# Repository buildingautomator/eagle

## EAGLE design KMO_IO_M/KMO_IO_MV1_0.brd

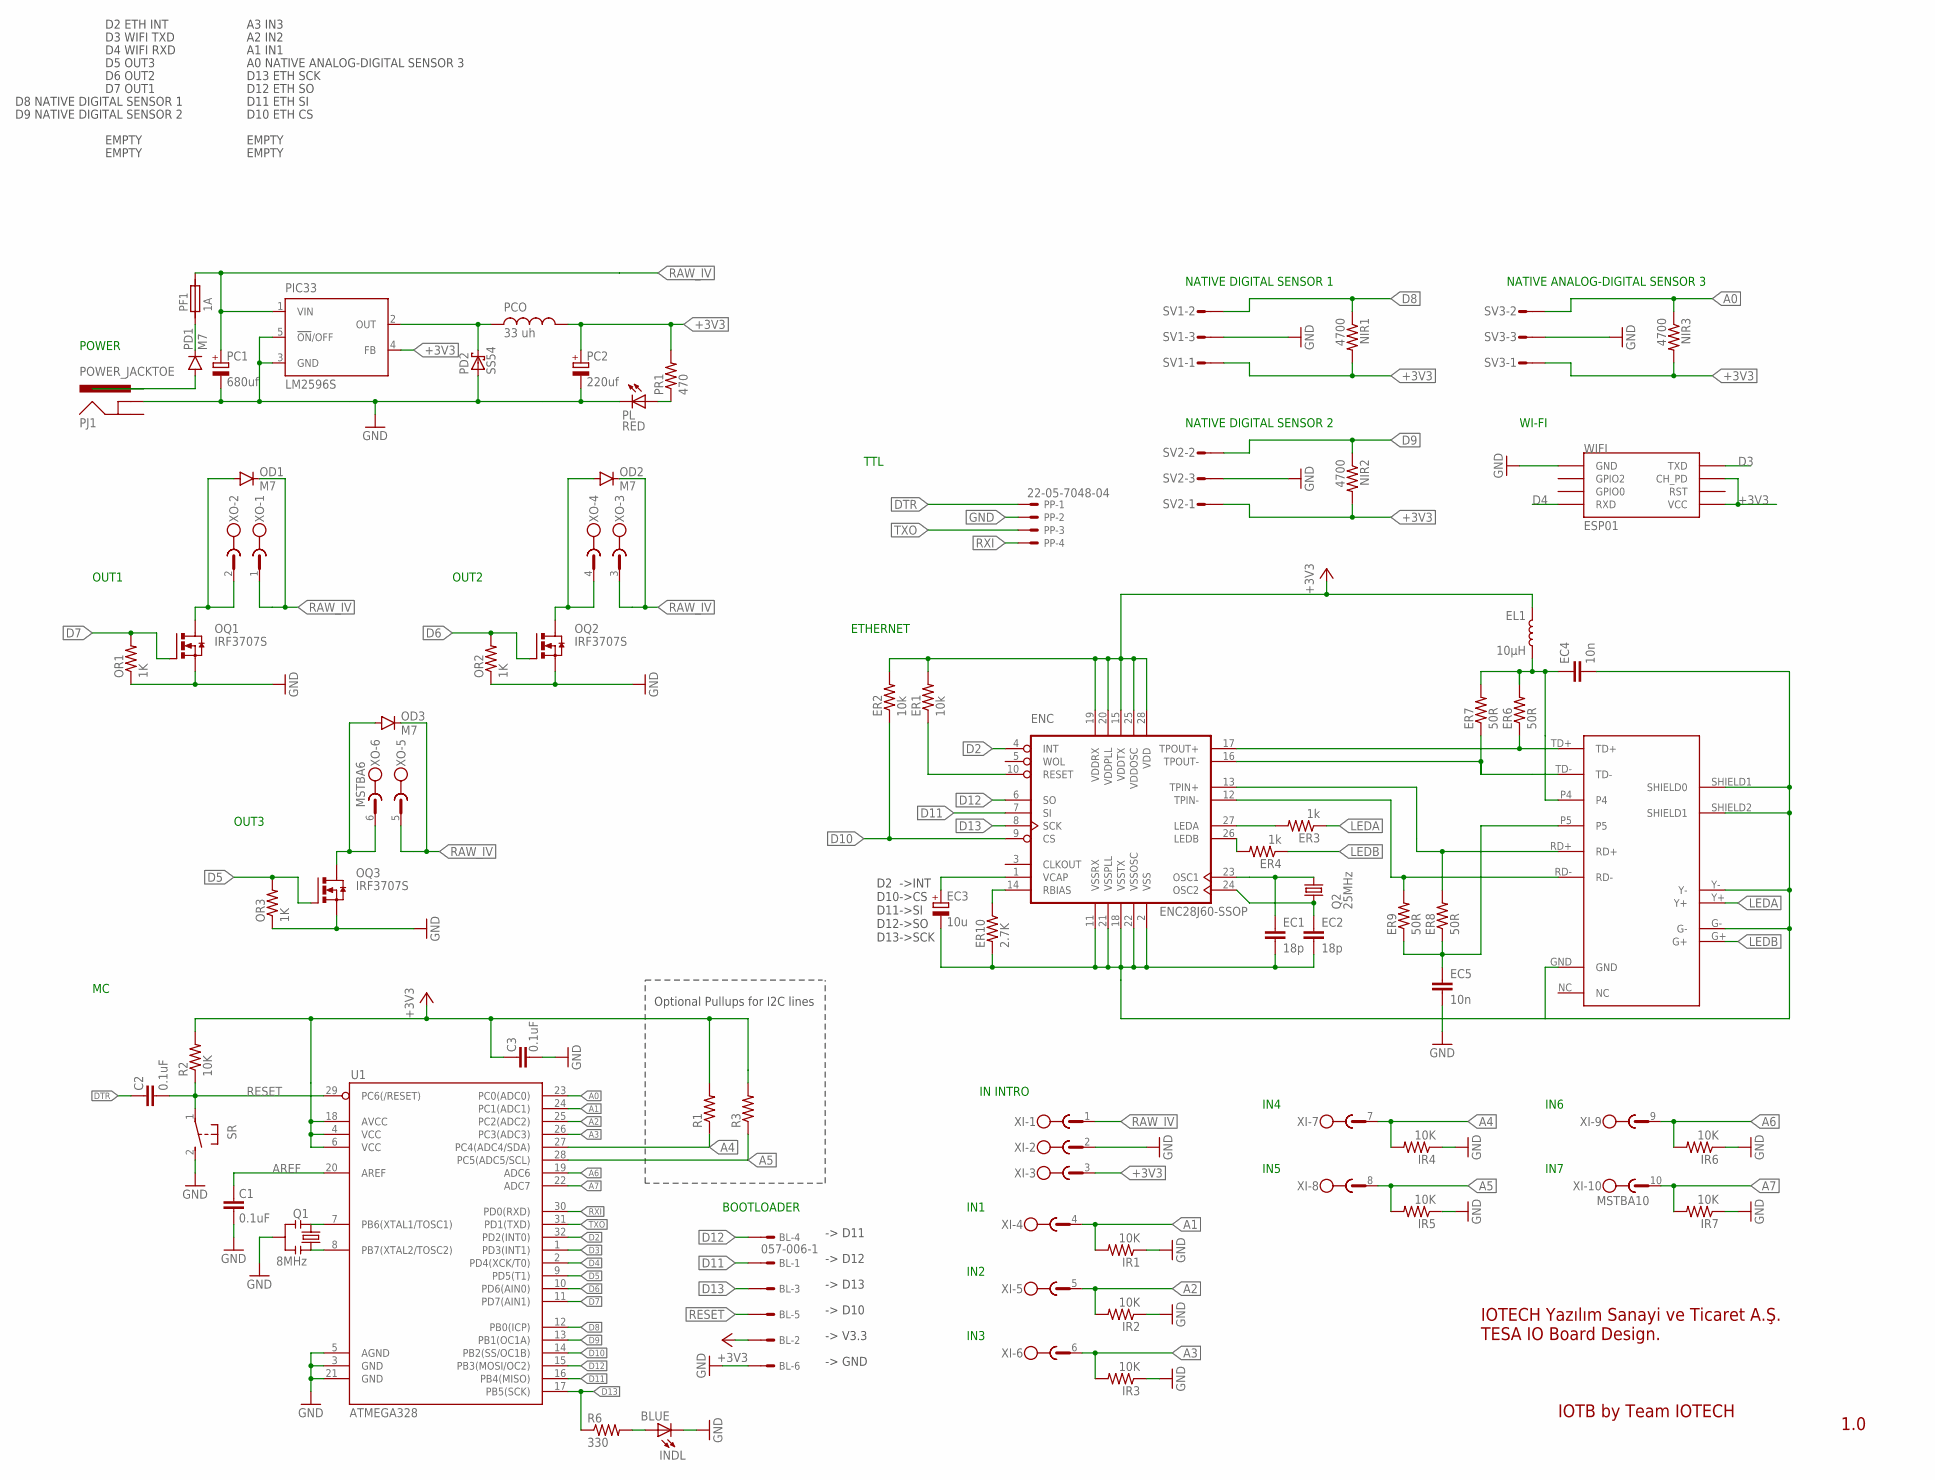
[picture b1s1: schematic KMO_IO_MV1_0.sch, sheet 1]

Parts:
BL: 057-006-1
C1, C2, C3: 0.1uF; 0805
EC1, EC2: 18p; 0805
EC3: 10u; CT3216
EC4, EC5: 10n; 0805
EL1: 10µH; 0805
ENC: ENC28J60-SSOP; SSOP28
ER1, ER2: 10k; 0805
ER3, ER4: 1k; 0805
ER6, ER7, ER8, ER9: 50R; 0805
ER10: 2.7K; 0805
INDL: BLUE; CHIP-LED0805
IR1, IR2, IR3, IR4, IR5, IR6, IR7: 10K; 0805
NIR1, NIR2, NIR3: 4700; 0805
OD1, OD2, OD3: M7; SMA-DIODE
OQ1, OQ2, OQ3: IRF3707S; D2PACK
OR1, OR2, OR3: 1K; 0805
PC1: 680uf; 140CLH-1010
PC2: 220uf; 140CLH-1010
PCO: 33 uh; MSS1260
PD1: M7; SMA-DIODE
PD2: SS54; SMB
PF1: 1A; 1820
PIC33: LM2596S; TO263-5
PJ1: POWER_JACKTOE; POWER_JACK_SMD_OVERPASTE_TOE
PL: RED; CHIP-LED0805
PP: 22-05-7048-04; 7395-04
PR1: 470; 0805
Q1: 8MHz; RESONATOR-SMD-1:1
Q2: 25MHz; 5.0X3.2_2
R1, R3: RESISTOR0805-RES; 0805
R2: 10K; 0805
R6: 330; 0805
SR: 31-XX; B3F-31XX
SV1, SV2, SV3: S03P
U1: ATMEGA328; TQFP32-08
U$2: HR911105A; RJ45
WIFI: ESP01
XI: MSTBA10
XO: MSTBA6

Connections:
+3V3: BL.2, C3.2, EL1.1, ENC.15 (VDDTX), ENC.19 (VDDRX), ENC.20 (VDDPLL), ENC.25 (VDDOSC), ENC.28 (VDD), ER1.2, ER2.2, NIR1.2, NIR2.2, NIR3.2, PC2.+, PCO.P$1, PIC33.4 (FB), PR1.2, R1.2, R2.2, R3.2, SV1.1, SV2.1, SV3.1, U1.4 (VCC), U1.6 (VCC), U1.18 (AVCC), WIFI.CH_PD, WIFI.VCC, XI.3
A0: NIR3.1, SV3.2, U1.23 (PC0(ADC0))
A1: IR1.2, U1.24 (PC1(ADC1)), XI.4
A2: IR2.2, U1.25 (PC2(ADC2)), XI.5
A3: IR3.2, U1.26 (PC3(ADC3)), XI.6
A4: IR4.2, R1.1, U1.27 (PC4(ADC4/SDA)), XI.7
A5: IR5.2, R3.1, U1.28 (PC5(ADC5/SCL)), XI.8
A6: IR6.2, U1.19 (ADC6), XI.9
A7: IR7.2, U1.22 (ADC7), XI.10
AREF: C1.2, U1.20 (AREF)
D2: ENC.4 (INT), U1.32 (PD2(INT0))
D3: U1.1 (PD3(INT1)), WIFI.TX (TXD)
D4: U1.2 (PD4(XCK/T0)), WIFI.RX (RXD)
D5: OQ3.1 (G), OR3.2, U1.9 (PD5(T1))
D6: OQ2.1 (G), OR2.2, U1.10 (PD6(AIN0))
D7: OQ1.1 (G), OR1.2, U1.11 (PD7(AIN1))
D8: NIR1.1, SV1.2, U1.12 (PB0(ICP))
D9: NIR2.1, SV2.2, U1.13 (PB1(OC1A))
D10: ENC.9 (CS), ER2.1, U1.14 (PB2(SS/OC1B))
D11: BL.1, ENC.7 (SI), U1.16 (PB4(MISO))
D12: BL.4, ENC.6 (SO), U1.15 (PB3(MOSI/OC2))
D13: BL.3, ENC.8 (SCK), R6.1, U1.17 (PB5(SCK))
DTR: C2.2, PP.1
EP4: EC4.1, EL1.2, ER6.2, ER7.2, U$2.P4
EP5: EC5.1, ER8.1, ER9.1, U$2.P5
GND: BL.6, C1.1, C3.1, EC1.2, EC2.2, EC3.-, EC4.2, EC5.2, ENC.2 (VSS), ENC.11 (VSSRX), ENC.18 (VSSTX), ENC.21 (VSSPLL), ENC.22 (VSSOSC), ER10.2, INDL.C, IR1.1, IR2.1, IR3.1, IR4.1, IR5.1, IR6.1, IR7.1, OQ1.3 (S), OQ2.3 (S), OQ3.3 (S), OR1.1, OR2.1, OR3.1, PC1.-, PC2.-, PD2.A, PIC33.3 (GND), PIC33.5 (!ON!/OFF), PJ1.GND (GNDBREAK), PL.C, PP.2, Q1.2, SR.2 (S), SV1.3, SV2.3, SV3.3, U1.3 (GND), U1.5 (AGND), U1.21 (GND), U$2.G-, U$2.GND, U$2.SHIELD1 (SHIELD0), U$2.SHIELD2 (SHIELD1), U$2.Y-, WIFI.GND, XI.2
LEDA: ER3.1, U$2.Y+
LEDB: ER4.1, U$2.G+
unnamed: OD3.A, OQ3.2 (D), XO.6
unnamed: PD1.C, PF1.1
unnamed: OD1.A, OQ1.2 (D), XO.2
unnamed: OD2.A, OQ2.2 (D), XO.4
unnamed: INDL.A, R6.2
unnamed: ENC.27 (LEDA), ER3.2
unnamed: Q1.3, U1.8 (PB7(XTAL2/TOSC2))
unnamed: PL.A, PR1.1
unnamed: EC3.+, ENC.1 (VCAP)
unnamed: ENC.26 (LEDB), ER4.2
unnamed: Q1.1, U1.7 (PB6(XTAL1/TOSC1))
unnamed: PCO.P$2, PD2.C, PIC33.2 (OUT)
unnamed: ENC.10 (RESET), ER1.1
unnamed: PD1.A, PJ1.VIN0 (PWR)
unnamed: ENC.14 (RBIAS), ER10.1
unnamed: EC2.1, ENC.24 (OSC2), Q2.1
unnamed: EC1.1, ENC.23 (OSC1), Q2.2
RAW_IV: OD1.C, OD2.C, OD3.C, PC1.+, PF1.2, PIC33.1 (VIN), XI.1, XO.1, XO.3, XO.5
RD+: ENC.13 (TPIN+), ER8.2, U$2.RD+
RD-: ENC.12 (TPIN-), ER9.2, U$2.RD-
RESET: BL.5, C2.1, R2.1, SR.1, U1.29 (PC6(/RESET))
RXI: PP.4, U1.30 (PD0(RXD))
TD+: ENC.17 (TPOUT+), ER6.1, U$2.TD+
TD-: ENC.16 (TPOUT-), ER7.1, U$2.TD-
TXO: PP.3, U1.31 (PD1(TXD))

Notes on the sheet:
POWER
OUT1
NATIVE DIGITAL SENSOR 1
IN INTRO
NATIVE DIGITAL SENSOR 2
OUT2
WI-FI
OUT3
NATIVE ANALOG-DIGITAL SENSOR 3
IN1
IN2
IN3
IOTB by Team IOTECH
1.0
ETHERNET
D2 ->INT D10->CS D11->SI D12->SO D13->SCK
TTL
IOTECH Yazılım Sanayi ve Ticaret A.Ş. TESA IO Board Design.
Optional Pullups for I2C lines
D2 ETH INT
D8 NATIVE DIGITAL SENSOR 1
D9 NATIVE DIGITAL SENSOR 2
EMPTY
A3 IN3
A2 IN2
A1 IN1
A0 NATIVE ANALOG-DIGITAL SENSOR 3
D13 ETH SCK
D12 ETH SO
D11 ETH SI
D10 ETH CS
D4 WIFI RXD
D3 WIFI TXD
D7 OUT1
D6 OUT2
D5 OUT3
IN4
IN5
IN6
IN7

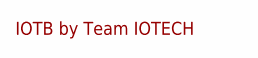
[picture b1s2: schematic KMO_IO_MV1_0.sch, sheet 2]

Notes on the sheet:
IOTB by Team IOTECH

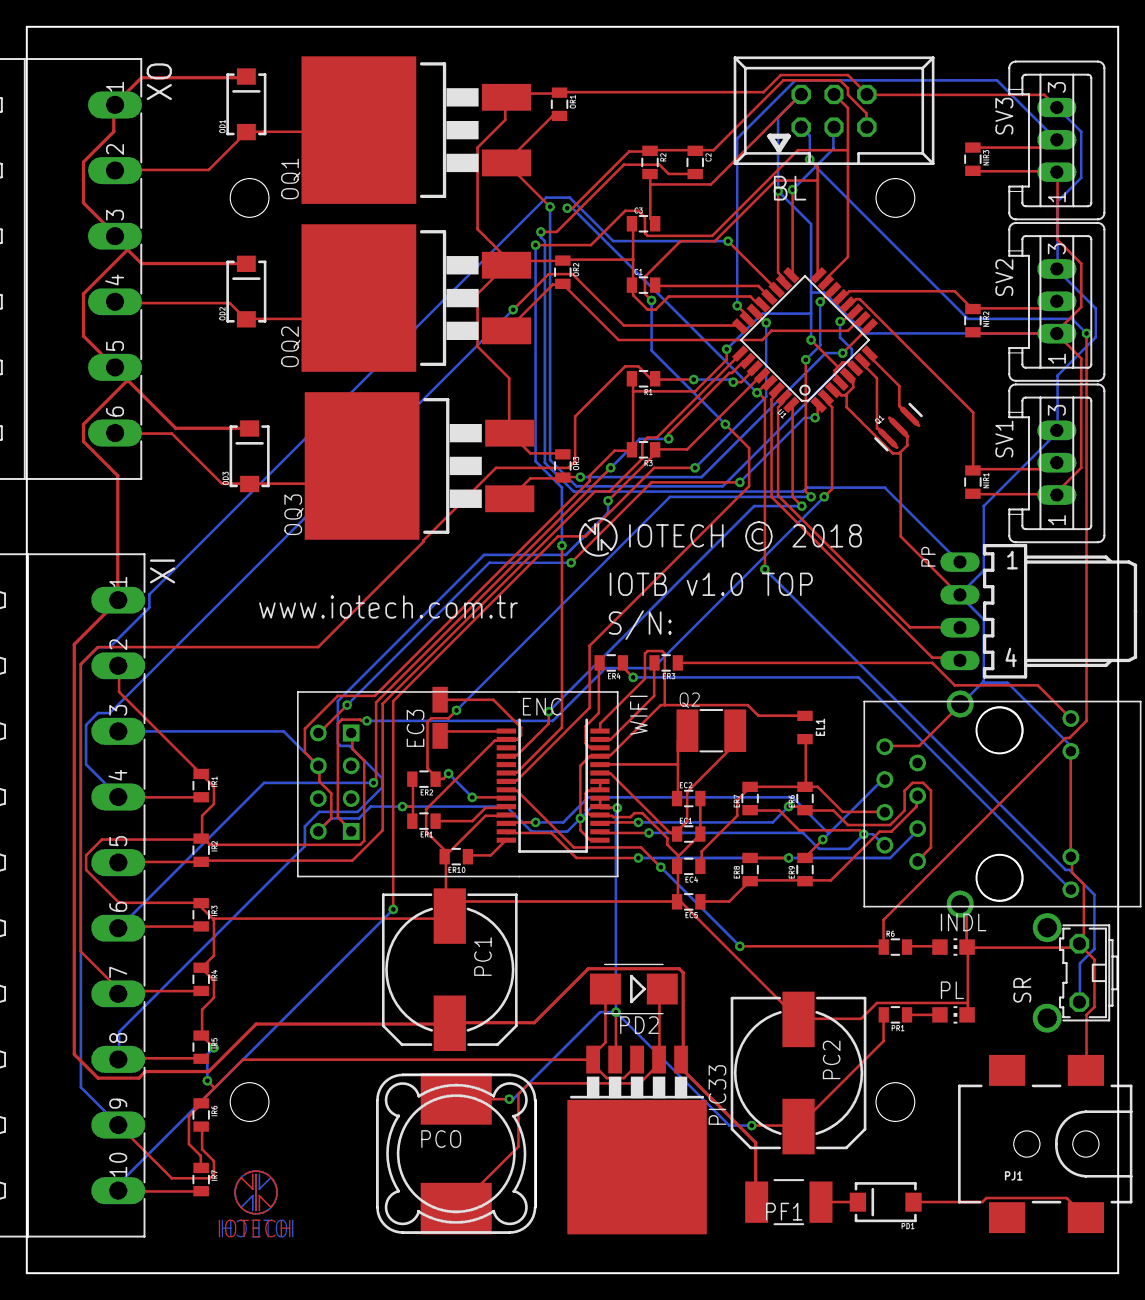
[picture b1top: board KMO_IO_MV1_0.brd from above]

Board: 2 copper layers, 84.5 x 96.5 mm, 68 parts (1 on the bottom side), 53 nets.

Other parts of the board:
U$1, U$4: IOTECH_COPPER_W_TEXT

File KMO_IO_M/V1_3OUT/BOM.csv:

Part,Value,Device,Package,Description                                                             MF                     MPN              OC_FARNELL OC_NEWARK PROD_ID    SF_ID     SPICEPREFIX VALUEBL,057-006-1,057-006-1,057-006-1,CONNECTOR                                                                                                       unknown    unknownBLS,,SW_DIP-1,EDG-01,DIP SWITCHC1,100nF,CAP0805,805,CapacitorC2,100nF,CAP0805,805,CapacitorC3,100nF,CAP0805,805,CapacitorEC1,18p,CAP0805,805,CapacitorEC2,18p,CAP0805,805,CapacitorEC3,10u,CPOL-EUCT3216,CT3216,"POLARIZED CAPACITOR, European symbol                                                                                                                      C"EC4,10n,CAP0805,805,CapacitorEC5,10n,CAP0805,805,CapacitorEL1,10µH,INDUCTOR-0805-3.3UH,805,Inductors                                                                                                                            NDUC-13076                       3.3µH/±20%/450mAENC,ENC28J60-SSOP,ENC28J60-SSOP,SSOP28,Microchip 10Mbit Eth. contoller with SPI interfaceER1,10k,RESISTOR0805-RES,805,ResistorER2,10k,RESISTOR0805-RES,805,ResistorER3,1k,RESISTOR0805-RES,805,ResistorER4,1k,RESISTOR0805-RES,805,ResistorER6,50R,RESISTOR0805-RES,805,ResistorER7,50R,RESISTOR0805-RES,805,ResistorER8,50R,RESISTOR0805-RES,805,ResistorER9,50R,RESISTOR0805-RES,805,ResistorER10,2.7K,RESISTOR0805-RES,805,ResistorIL1,BLU,LEDCHIP-LED0805,CHIP-LED0805,LEDIL2,BLU,LEDCHIP-LED0805,CHIP-LED0805,LEDIL3,BLU,LEDCHIP-LED0805,CHIP-LED0805,LEDIL4,BLU,LEDCHIP-LED0805,CHIP-LED0805,LEDIL5,BLU,LEDCHIP-LED0805,CHIP-LED0805,LEDIL6,BLU,LEDCHIP-LED0805,CHIP-LED0805,LEDIL7,BLU,LEDCHIP-LED0805,CHIP-LED0805,LEDINDL,BLU,LEDCHIP-LED0805,CHIP-LED0805,LEDIR,10K,RESISTOR0805-RES,805,ResistorIR1,1K,RESISTOR0805-RES,805,ResistorIR2,1K,RESISTOR0805-RES,805,ResistorIR3,1K,RESISTOR0805-RES,805,ResistorIR4,1K,RESISTOR0805-RES,805,ResistorIR5,1K,RESISTOR0805-RES,805,ResistorIR6,1K,RESISTOR0805-RES,805,ResistorIR7,1K,RESISTOR0805-RES,805,Resistor,,,,,,,,,,,,OD1,M7,DIODESMA,SMA-DIODE,DiodeOD2,M7,DIODESMA,SMA-DIODE,DiodeOD3,M7,DIODESMA,SMA-DIODE,DiodeOL1,YLW,LEDCHIP-LED0805,CHIP-LED0805,LEDOL2,YLW,LEDCHIP-LED0805,CHIP-LED0805,LEDOL3,YLW,LEDCHIP-LED0805,CHIP-LED0805,LEDOQ1,IRF3707S,IRF3704S,D2PACK,SMPS MOSFETOQ2,IRF3707S,IRF3704S,D2PACK,SMPS MOSFETOQ3,IRF3707S,IRF3704S,D2PACK,SMPS MOSFETOR1,1K,RESISTOR0805-RES,805,ResistorOR2,1K,RESISTOR0805-RES,805,ResistorOR3,1K,RESISTOR0805-RES,805,ResistorPC1,470uf 25v,CPOL-EU140CLH-1010,140CLH-1010,"POLARIZED CAPACITOR, European symbol                                                                                                                      C"PC2,220uf 50v,CPOL-EU140CLH-1010,140CLH-1010,"POLARIZED CAPACITOR, European symbol                                                                                                                      C"PCO,220 uh,MSS1260,MSS1260,SMT Power InductorPD1,M7,DIODESMA,SMA-DIODE,DiodePD2,SS54,SCHOTTKY-DIODESMD,SMB,Schottky DiodePF1,1A,SIBA194600,1820,"SIBA PTC-Fuses, Series 194600, 1812 (4.5 3.2)mm"PIC33,LM2596S,LM2596S,TO263-5,SIMPLE SWITCHER¨ Power Converter 150 kHz 3A Step-Down Voltage Regulator NATIONAL SEMICONDUCTOR LM2596S-ADJ/NOPB 9494367    41K3842PJ1,POWER_JACKTOE,POWER_JACKTOE,POWER_JACK_SMD_OVERPASTE_TOE,Power Jack Connector                                                                                                                 CONN-08106 PRT-12748PL,GRN,LEDCHIP-LED0805,CHIP-LED0805,LEDPP,22-05-7048-04,22-05-7048-04,7395-04,CONNECTOR                                                               MOLEX                                   unknown    unknown          90 Degree horizontalPR1,1k,RESISTOR0805-RES,805,ResistorQ1,8MHz,RESONATOR1:1,RESONATOR-SMD-1:1,ResonatorQ2,25MHz,KX-9B,5.0X3.2_2,Quartz Crystals (MHz) SMD:,,,,R2,10K,RESISTOR0805-RES,805,Resistor,,,,R6,1k,RESISTOR0805-RES,805,ResistorSR,,31-XX,B3F-31XX,OMRON SWITCH                                                                                   B3F-3100         959704     36M3582SV1,,S03P,S03P,AMP MT CONNECTOR 90 Degree horizontalSV2,,S03P,S03P,AMP MT CONNECTOR 90 Degree horizontalSV3,,S03P,S03P,AMP MT CONNECTOR 90 Degree horizontalU$2,HR911105A,HR911105A,RJ45,U1,ATMEGA328,ATMEGA168,TQFP32-08,,,,,WIL0,BLU,LEDCHIP-LED0805,CHIP-LED0805,LEDWIL2,BLU,LEDCHIP-LED0805,CHIP-LED0805,LEDWIR0,1K,RESISTOR0805-RES,805,ResistorWIR2,1K,RESISTOR0805-RES,805,ResistorX1,MC3,MC3,MC3,Mini-Combicon 3.81mm horizontal 3-poligXI,MC10,MC10,MC10,Mini-Combicon 3.81mm horizontal 10-poligXO,MC6,MC6,MC6,Mini-Combicon 3.81mm horizontal 6-polig

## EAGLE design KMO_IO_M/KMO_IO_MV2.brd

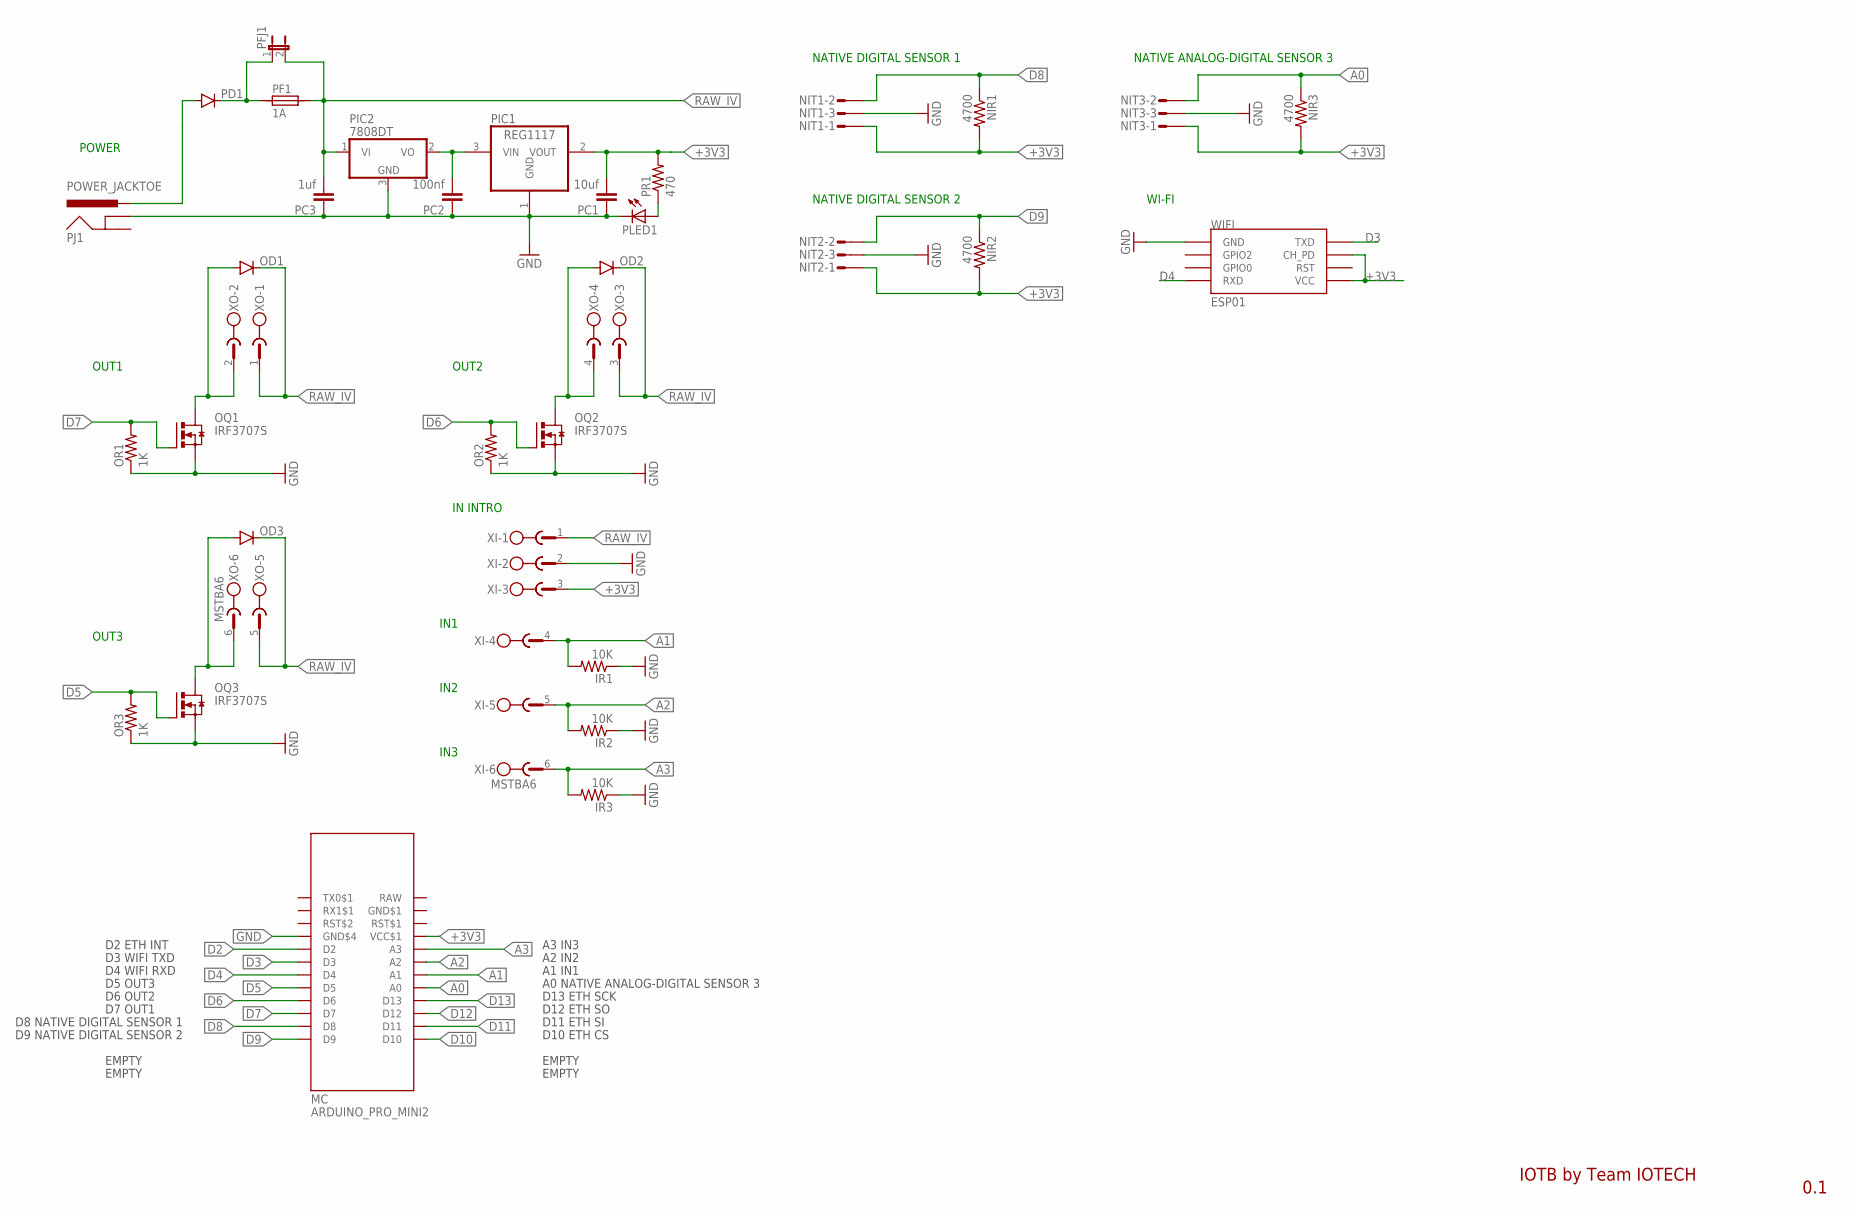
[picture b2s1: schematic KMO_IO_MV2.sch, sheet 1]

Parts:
IR1, IR2, IR3: 10K; 0805
MC: ARDUINO_PRO_MINI2
NIR1, NIR2, NIR3: 4700; 0805
NIT1, NIT2, NIT3: S03P
OD1, OD2, OD3: DIODESMA; SMA-DIODE
OQ1, OQ2, OQ3: IRF3707S; D2PACK
OR1, OR2, OR3: 1K; 0805
PC1: 10uf; 0805
PC2: 100nf; 0805
PC3: 1uf; 0805
PD1: DIODESMA; SMA-DIODE
PF1: 1A; 1820
PFJ1: JP1E; JP1
PIC1: REG1117; SOT223
PIC2: 7808DT; TO252
PJ1: POWER_JACKTOE; POWER_JACK_SMD_OVERPASTE_TOE
PLED1: LEDCHIP-LED0805; CHIP-LED0805
PR1: 470; 0805
WIFI: ESP01
XI: MSTBA6
XO: MSTBA6

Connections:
+3V3: MC.VCC$1, NIR1.2, NIR2.2, NIR3.2, NIT1.1, NIT2.1, NIT3.1, PC1.2, PIC1.2 (VOUT), PR1.2, WIFI.CH_PD, WIFI.VCC, XI.3; also elsewhere on the board
A0: MC.A0, NIR3.1, NIT3.2
A1: IR1.2, MC.A1, XI.4
A2: IR2.2, MC.A2, XI.5
A3: IR3.2, MC.A3, XI.6
D2: MC.D2; also elsewhere on the board
D3: MC.D3, WIFI.TX (TXD)
D4: MC.D4, WIFI.RX (RXD)
D5: MC.D5, OQ3.1 (G), OR3.2
D6: MC.D6, OQ2.1 (G), OR2.2
D7: MC.D7, OQ1.1 (G), OR1.2
D8: MC.D8, NIR1.1, NIT1.2
D9: MC.D9, NIR2.1, NIT2.2
D10: MC.D10; also elsewhere on the board
D11: MC.D11; also elsewhere on the board
D12: MC.D12; also elsewhere on the board
D13: MC.D13; also elsewhere on the board
GND: IR1.1, IR2.1, IR3.1, MC.GND$4, NIT1.3, NIT2.3, NIT3.3, OQ1.3 (S), OQ2.3 (S), OQ3.3 (S), OR1.1, OR2.1, OR3.1, PC1.1, PC2.1, PC3.1, PIC1.1 (GND), PIC2.3 (GND), PJ1.GND (GNDBREAK), PLED1.C, WIFI.GND, XI.2; also elsewhere on the board
GND$1: MC.GDN$1 (GND$1)
unnamed: OD3.A, OQ3.2 (D), XO.6
unnamed: PD1.C, PF1.1, PFJ1.1
unnamed: OD1.A, OQ1.2 (D), XO.2
unnamed: OD2.A, OQ2.2 (D), XO.4
unnamed: PD1.A, PJ1.VIN0 (PWR)
unnamed: PLED1.A, PR1.1
unnamed: PC2.2, PIC1.3 (VIN), PIC2.2 (VO)
RAW: MC.RAW
RAW_IV: OD1.C, OD2.C, OD3.C, PC3.2, PF1.2, PFJ1.2, PIC2.1 (VI), XI.1, XO.1, XO.3, XO.5

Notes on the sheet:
POWER
OUT1
NATIVE DIGITAL SENSOR 1
IN INTRO
NATIVE DIGITAL SENSOR 2
OUT2
WI-FI
D2 ETH INT
D8 NATIVE DIGITAL SENSOR 1
D9 NATIVE DIGITAL SENSOR 2
EMPTY
A3 IN3
A2 IN2
A1 IN1
A0 NATIVE ANALOG-DIGITAL SENSOR 3
D13 ETH SCK
D12 ETH SO
D11 ETH SI
D10 ETH CS
OUT3
D4 WIFI RXD
D3 WIFI TXD
D7 OUT1
D6 OUT2
D5 OUT3
NATIVE ANALOG-DIGITAL SENSOR 3
IN1
IN2
IN3
IOTB by Team IOTECH
0.1

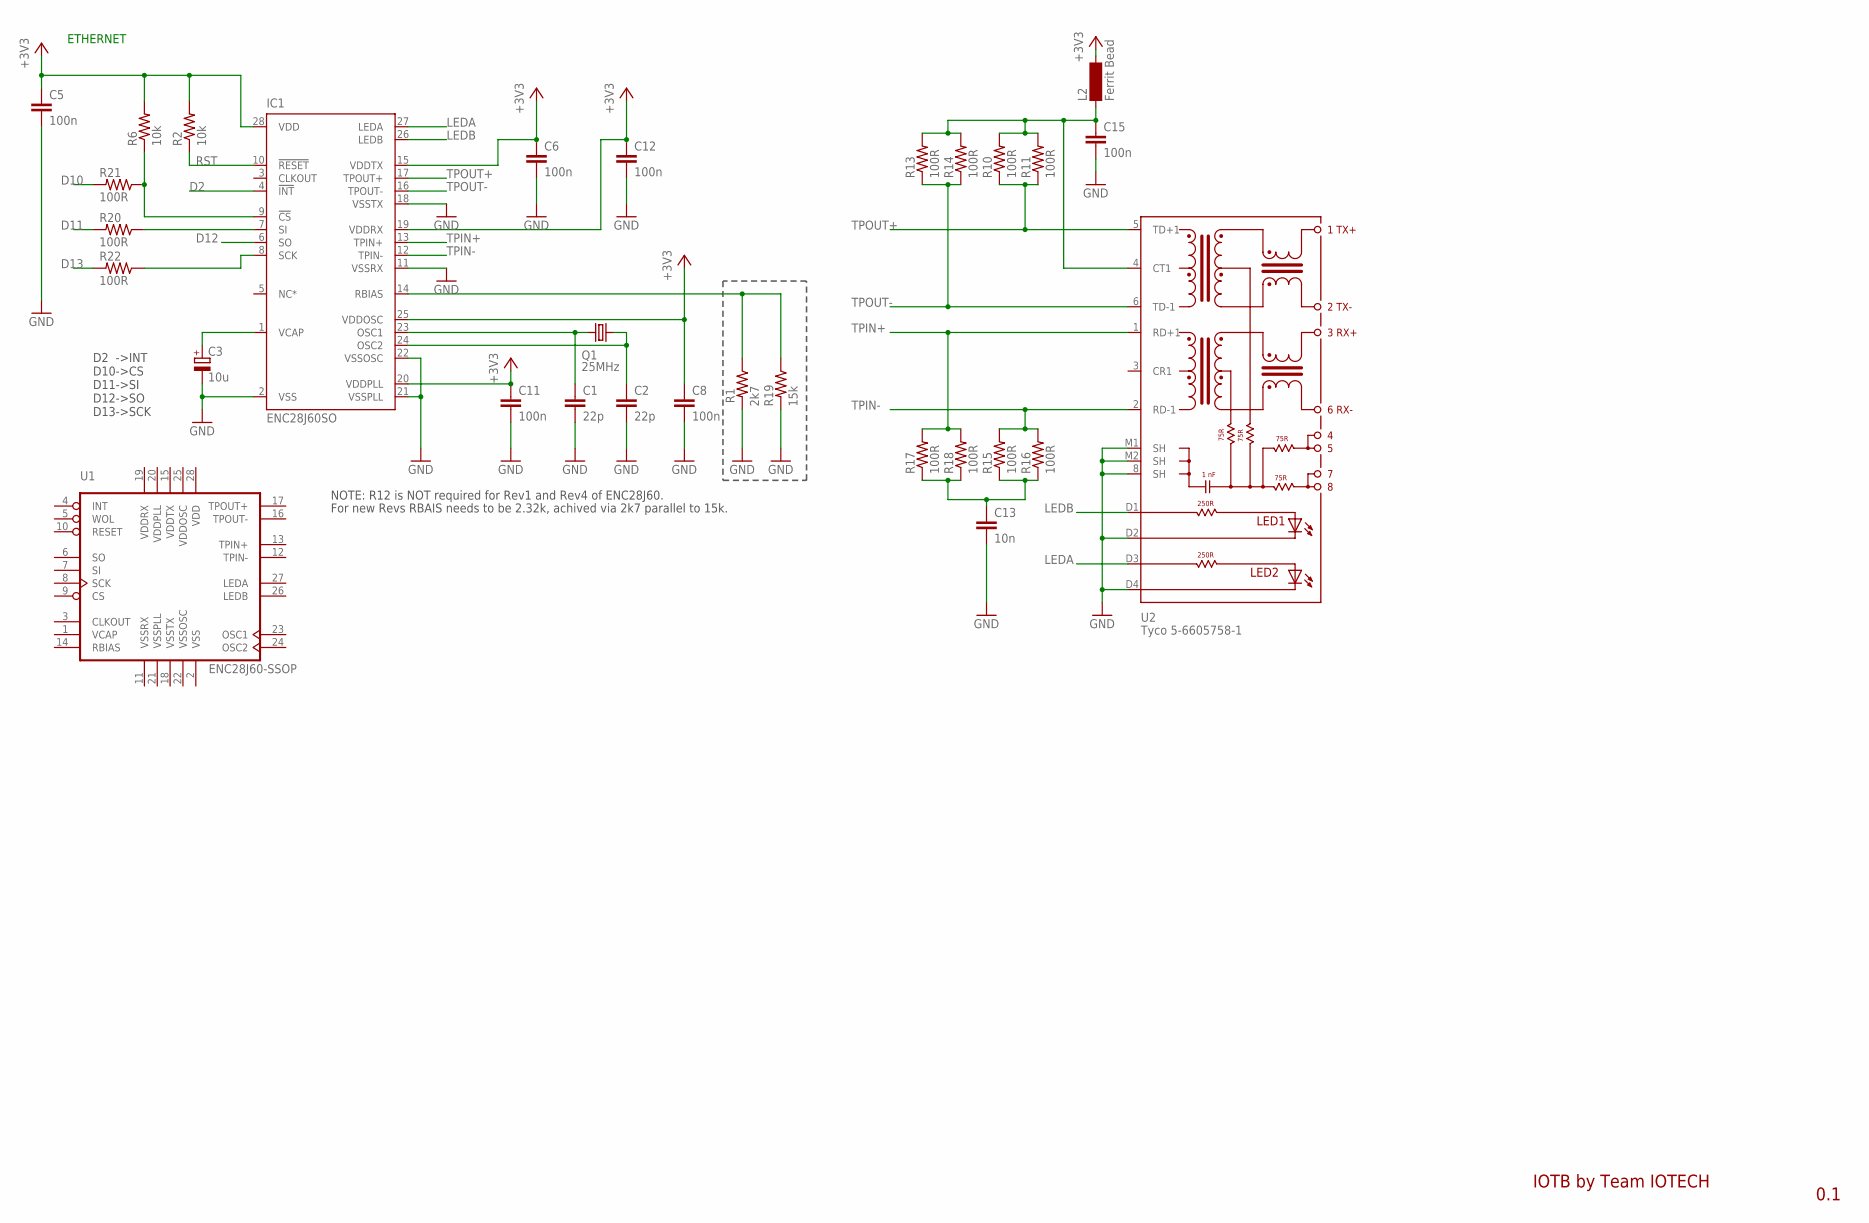
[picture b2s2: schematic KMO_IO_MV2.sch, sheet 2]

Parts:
C1, C2: 22p; 0805
C3: 10u; E2,5-5
C5, C6, C8, C11, C12, C15: 100n; 0805
C13: 10n; 0805
IC1: ENC28J60SO; SO28W
L2: Ferrit Bead; SM-1206
Q1: 25MHz; HC49/S
R1: 2k7; 0805
R2, R6: 10k; 0805
R10, R11, R13, R14, R15, R16, R17, R18, R20, R21, R22: 100R; 0805
R19: 15k; 0805
U1: ENC28J60-SSOP; SSOP28
U2: Tyco 5-6605758-1; 5-6605758-1

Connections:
+3V3: C5.1, C6.1, C8.1, C11.1, C12.1, IC1.15 (VDDTX), IC1.19 (VDDRX), IC1.20 (VDDPLL), IC1.25 (VDDOSC), IC1.28 (VDD), L2.2, R2.2, R6.2; also elsewhere on the board
D2: IC1.4 (!INT); also elsewhere on the board
D10: R21.2; also elsewhere on the board
D11: R20.2; also elsewhere on the board
D12: IC1.6 (SO); also elsewhere on the board
D13: R22.2; also elsewhere on the board
GND: C1.2, C2.2, C3.-, C5.2, C6.2, C8.2, C11.2, C12.2, C13.2, C15.2, IC1.2 (VSS), IC1.11 (VSSRX), IC1.18 (VSSTX), IC1.21 (VSSPLL), IC1.22 (VSSOSC), R1.2, R19.2, U2.8 (SH), U2.D2, U2.D4, U2.M1 (SH), U2.M2 (SH); also elsewhere on the board
LEDA: IC1.27 (LEDA), U2.D3
LEDB: IC1.26 (LEDB), U2.D1
unnamed: C1.1, IC1.23 (OSC1), Q1.1
unnamed: C2.1, IC1.24 (OSC2), Q1.2
unnamed: C3.+, IC1.1 (VCAP)
unnamed: IC1.14 (RBIAS), R1.1, R19.1
unnamed: C13.1, R15.1, R16.1, R17.1, R18.1
unnamed: C15.1, L2.1, R10.2, R11.2, R13.2, R14.2, U2.4 (CT1)
unnamed: IC1.7 (SI), R20.1
unnamed: IC1.9 (!CS), R6.1, R21.1
unnamed: IC1.8 (SCK), R22.1
RST: IC1.10 (!RESET), R2.1
TPIN+: IC1.13 (TPIN+), R17.2, R18.2, U2.1 (RD+1)
TPIN-: IC1.12 (TPIN-), R15.2, R16.2, U2.2 (RD-1)
TPOUT+: IC1.17 (TPOUT+), R10.1, R11.1, U2.5 (TD+1)
TPOUT-: IC1.16 (TPOUT-), R13.1, R14.1, U2.6 (TD-1)
VCAP: U1.1 (VCAP)
VDD: U1.28 (VDD)
VDDOSC: U1.25 (VDDOSC)
VDDPLL: U1.20 (VDDPLL)
VDDRX: U1.19 (VDDRX)
VDDTX: U1.15 (VDDTX)
VSS: U1.2 (VSS)
VSSOSC: U1.22 (VSSOSC)
VSSPLL: U1.21 (VSSPLL)
VSSRX: U1.11 (VSSRX)
VSSTX: U1.18 (VSSTX)

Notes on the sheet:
ETHERNET
NOTE: R12 is NOT required for Rev1 and Rev4 of ENC28J60.
For new Revs RBAIS needs to be 2.32k, achived via 2k7 parallel to 15k.
IOTB by Team IOTECH
0.1
D2 ->INT D10->CS D11->SI D12->SO D13->SCK

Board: 2 copper layers, 63 parts (0 on the bottom side), 42 nets, no tracks yet.

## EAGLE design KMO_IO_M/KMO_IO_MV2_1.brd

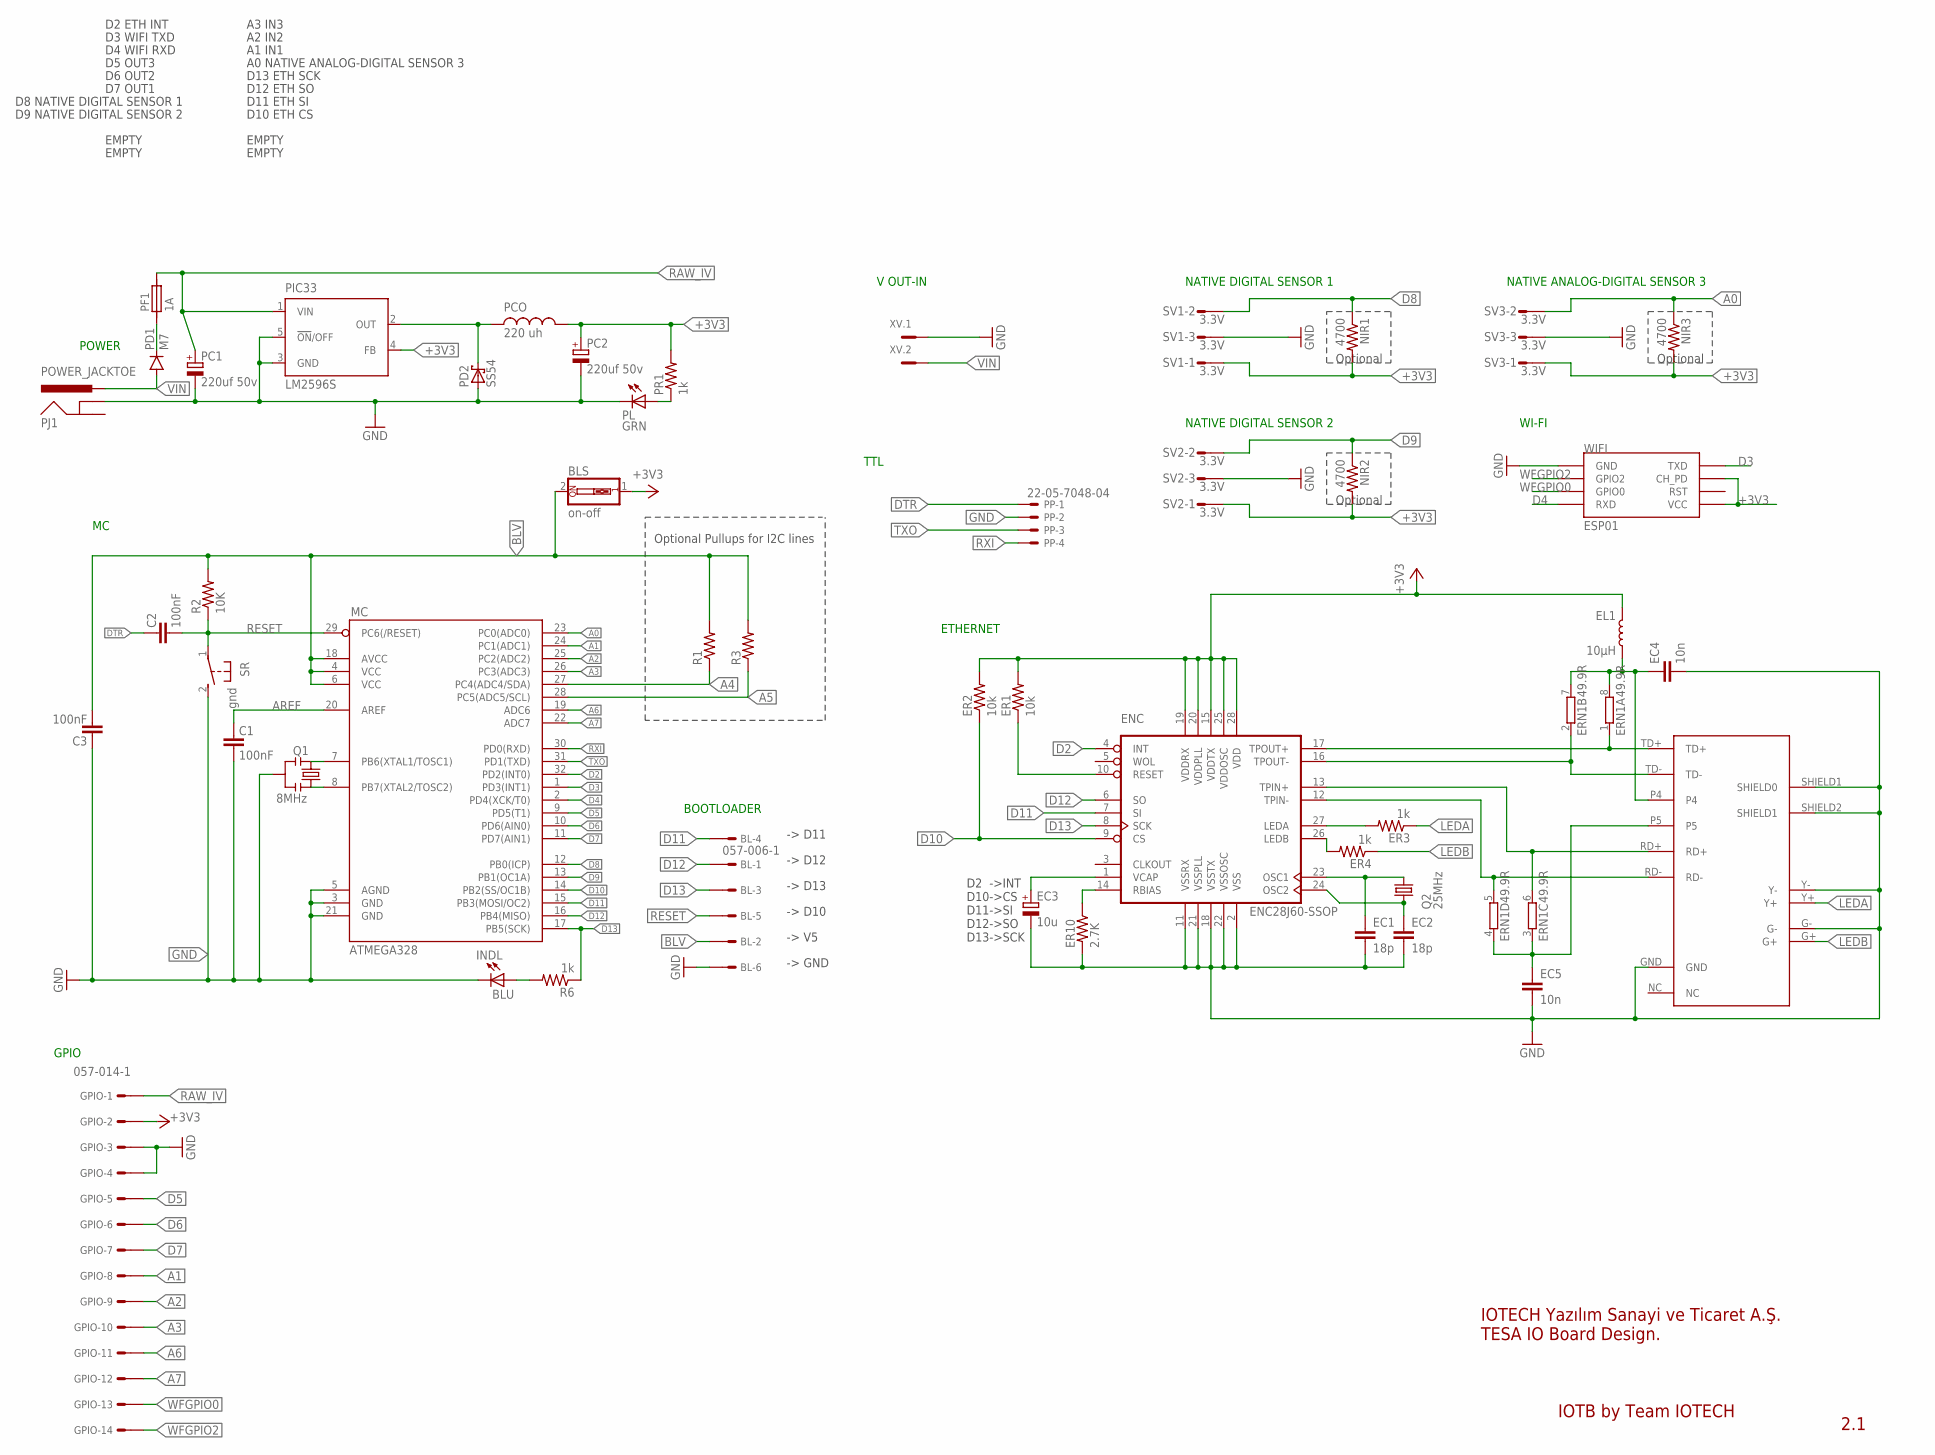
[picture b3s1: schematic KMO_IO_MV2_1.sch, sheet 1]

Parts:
BL: 057-006-1
BLS: on-off; EDG-01
C1, C2, C3: 100nF; 0805
EC1, EC2: 18p; 0805
EC3: 10u; CT3216
EC4, EC5: 10n; 0805
EL1: 10µH; 0805
ENC: ENC28J60-SSOP; SSOP28
ER1, ER2: 10k; 0805
ER3, ER4: 1k; 0805
ER10: 2.7K; 0805
ERN1: 49.9R; 0603-ARV
GPIO: 057-014-1
INDL: BLU; CHIP-LED0805
MC: ATMEGA328; TQFP32-08
NIR1, NIR2, NIR3: 4700; 0805
PC1, PC2: 220uf 50v; 140CLH-1010
PCO: 220 uh; MSS1260
PD1: M7; SMA-DIODE
PD2: SS54; SMB
PF1: 1A; 1820
PIC33: LM2596S; TO263-5
PJ1: POWER_JACKTOE; POWER_JACK_SMD_OVERPASTE_TOE
PL: GRN; CHIP-LED0805
PP: 22-05-7048-04; 7395-04
PR1: 1k; 0805
Q1: 8MHz; RESONATOR-SMD-1:1
Q2: 25MHz; 5.0X3.2_2
R1, R3: RESISTOR0805-RES; 0805
R2: 10K; 0805
R6: 1k; 0805
SR: gnd; B3F-31XX
SV1, SV2, SV3: 3.3V; S03P
U$2: HR911105A; RJ45
WIFI: ESP01
XV: MC2

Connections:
+3V3: BLS.1, EL1.1, ENC.15 (VDDTX), ENC.19 (VDDRX), ENC.20 (VDDPLL), ENC.25 (VDDOSC), ENC.28 (VDD), ER1.2, ER2.2, GPIO.2, NIR1.2, NIR2.2, NIR3.2, PC2.+, PCO.P$1, PIC33.4 (FB), PR1.2, SV1.1, SV2.1, SV3.1, WIFI.CH_PD, WIFI.VCC; also elsewhere on the board
A0: MC.23 (PC0(ADC0)), NIR3.1, SV3.2
A1: GPIO.8, MC.24 (PC1(ADC1))
A2: GPIO.9, MC.25 (PC2(ADC2))
A3: GPIO.10, MC.26 (PC3(ADC3))
A4: MC.27 (PC4(ADC4/SDA)), R1.1; also elsewhere on the board
A5: MC.28 (PC5(ADC5/SCL)), R3.1; also elsewhere on the board
A6: GPIO.11, MC.19 (ADC6)
A7: GPIO.12, MC.22 (ADC7)
AREF: C1.2, MC.20 (AREF)
BLV: BL.2, BLS.2, C3.1, MC.4 (VCC), MC.6 (VCC), MC.18 (AVCC), R1.2, R2.2, R3.2
D2: ENC.4 (INT), MC.32 (PD2(INT0))
D3: MC.1 (PD3(INT1)), WIFI.TX (TXD)
D4: MC.2 (PD4(XCK/T0)), WIFI.RX (RXD)
D5: GPIO.5, MC.9 (PD5(T1))
D6: GPIO.6, MC.10 (PD6(AIN0))
D7: GPIO.7, MC.11 (PD7(AIN1))
D8: MC.12 (PB0(ICP)), NIR1.1, SV1.2
D9: MC.13 (PB1(OC1A)), NIR2.1, SV2.2
D10: ENC.9 (CS), ER2.1, MC.14 (PB2(SS/OC1B))
D11: BL.4, ENC.7 (SI), MC.15 (PB3(MOSI/OC2))
D12: BL.1, ENC.6 (SO), MC.16 (PB4(MISO))
D13: BL.3, ENC.8 (SCK), MC.17 (PB5(SCK)), R6.1
DTR: C2.2, PP.1
EP4: EC4.1, EL1.2, ERN1.7 (2), ERN1.8 (2), U$2.P4
EP5: EC5.1, ERN1.3 (1), ERN1.4 (1), U$2.P5
GND: BL.6, C1.1, C3.2, EC1.2, EC2.2, EC3.-, EC4.2, EC5.2, ENC.2 (VSS), ENC.11 (VSSRX), ENC.18 (VSSTX), ENC.21 (VSSPLL), ENC.22 (VSSOSC), ER10.2, GPIO.3, GPIO.4, INDL.C, MC.3 (GND), MC.5 (AGND), MC.21 (GND), PC1.-, PC2.-, PD2.A, PIC33.3 (GND), PIC33.5 (!ON!/OFF), PJ1.GND (GNDBREAK), PL.C, PP.2, Q1.2, SR.2 (S), SV1.3, SV2.3, SV3.3, U$2.G-, U$2.GND, U$2.SHIELD1 (SHIELD0), U$2.SHIELD2 (SHIELD1), U$2.Y-, WIFI.GND, XV.1; also elsewhere on the board
LEDA: ER3.1, U$2.Y+
LEDB: ER4.1, U$2.G+
unnamed: PD1.C, PF1.1
unnamed: INDL.A, R6.2
unnamed: ENC.27 (LEDA), ER3.2
unnamed: MC.8 (PB7(XTAL2/TOSC2)), Q1.3
unnamed: PL.A, PR1.1
unnamed: EC3.+, ENC.1 (VCAP)
unnamed: ENC.26 (LEDB), ER4.2
unnamed: MC.7 (PB6(XTAL1/TOSC1)), Q1.1
unnamed: PCO.P$2, PD2.C, PIC33.2 (OUT)
unnamed: ENC.10 (RESET), ER1.1
unnamed: ENC.14 (RBIAS), ER10.1
unnamed: EC2.1, ENC.24 (OSC2), Q2.1
unnamed: EC1.1, ENC.23 (OSC1), Q2.2
RAW_IV: GPIO.1, PC1.+, PF1.2, PIC33.1 (VIN)
RD+: ENC.13 (TPIN+), ERN1.6 (2), U$2.RD+
RD-: ENC.12 (TPIN-), ERN1.5 (2), U$2.RD-
RESET: BL.5, C2.1, MC.29 (PC6(/RESET)), R2.1, SR.1
RXI: MC.30 (PD0(RXD)), PP.4
TD+: ENC.17 (TPOUT+), ERN1.1, U$2.TD+
TD-: ENC.16 (TPOUT-), ERN1.2 (1), U$2.TD-
TXO: MC.31 (PD1(TXD)), PP.3
VIN: PD1.A, PJ1.VIN0 (PWR), XV.2
WFGPIO0: GPIO.13, WIFI.GPIO0
WFGPIO2: GPIO.14, WIFI.GPIO2

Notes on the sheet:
POWER
NATIVE DIGITAL SENSOR 1
NATIVE DIGITAL SENSOR 2
WI-FI
NATIVE ANALOG-DIGITAL SENSOR 3
IOTB by Team IOTECH
2.1
ETHERNET
D2 ->INT D10->CS D11->SI D12->SO D13->SCK
TTL
IOTECH Yazılım Sanayi ve Ticaret A.Ş. TESA IO Board Design.
Optional Pullups for I2C lines
D2 ETH INT
D8 NATIVE DIGITAL SENSOR 1
D9 NATIVE DIGITAL SENSOR 2
EMPTY
A3 IN3
A2 IN2
A1 IN1
A0 NATIVE ANALOG-DIGITAL SENSOR 3
D13 ETH SCK
D12 ETH SO
D11 ETH SI
D10 ETH CS
D4 WIFI RXD
D3 WIFI TXD
D7 OUT1
D6 OUT2
D5 OUT3
BOOTLOADER
-> D11
-> D12
-> D13
-> D10
-> V5
-> GND
Optional
V OUT-IN
GPIO

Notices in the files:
KMO_IO_M/KMO_IO_MV1_0.brd:
IOTECH © 2018
KMO_IO_M/KMO_IO_MV2_1.brd:
IOTECH © 2019
parts and their libraries:
SparkFun-DiscreteSemi: Licensing: Creative Commons ShareAlike 4.0 International - https://creativecommons.org/licenses/by-sa/4.0
crystal-geyer_V1_0: Copyright: Geyer-Electronic
